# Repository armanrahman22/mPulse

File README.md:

M-PULSE-Server
==============

Code repository for the m-pulse code residing on the server

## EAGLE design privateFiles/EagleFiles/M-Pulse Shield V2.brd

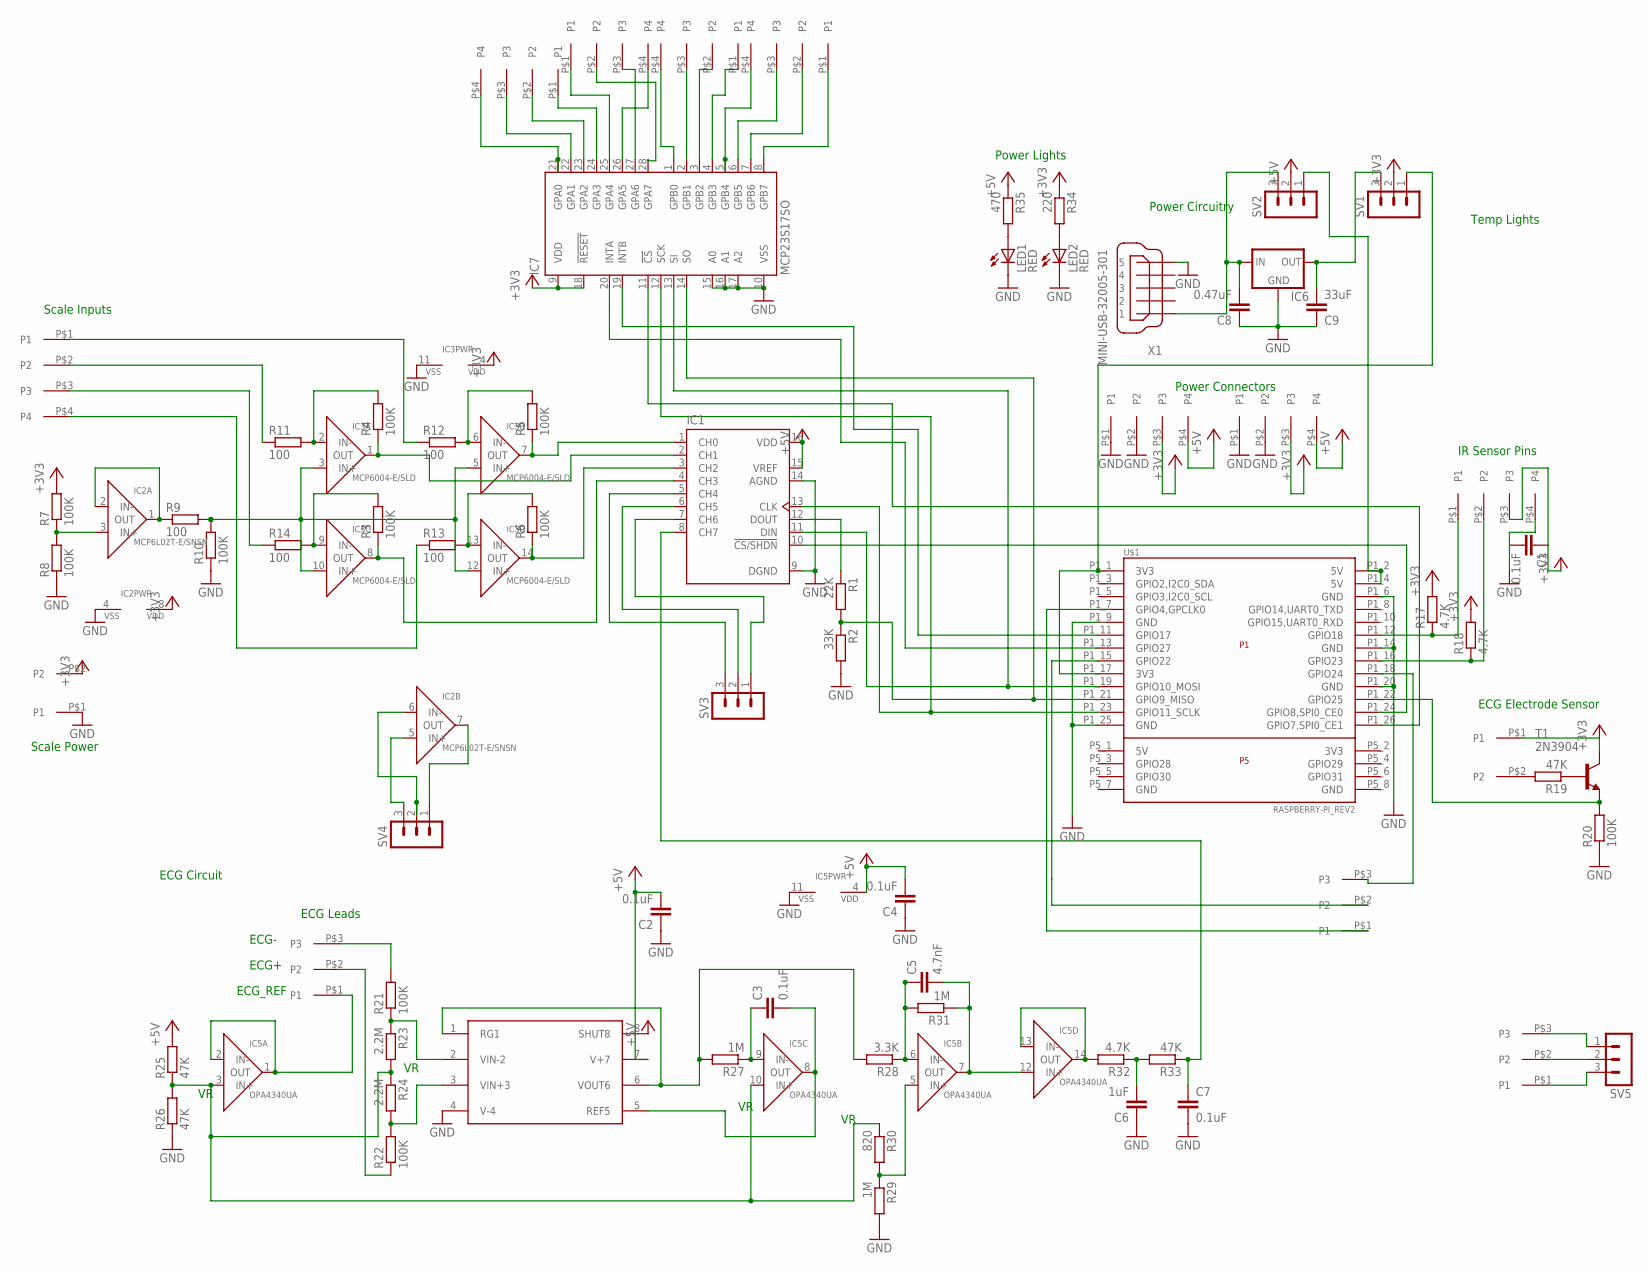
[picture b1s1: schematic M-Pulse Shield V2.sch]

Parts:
C1, C2, C3, C4, C7: 0.1uF; C0603
C5: 4.7nF; C0603
C6: 1uF; C0603
C8: 0.47uF; C0603
C9: 33uF; C0603
DIGITALPINS, DIGITALPINS1: 1776275-3
ECG_ES: 1776275-2
EKGLEADS: 1776275-3
I/O1, I/O2, I/O3, I/O4: 1776275-4
IC1: MCP3008; SOIC16N
IC2: MCP6L02T-E/SNSN; SO-08
IC3: MCP6004-E/SLD; SO14
IC4: INA321EAVSSOP-8; VSSOP-8
IC5: OPA4340UA; SO14
IC6: 78XXL
IC7: MCP23S17SO; SO28W
IR_I/O: 1776275-4
LED1, LED2: RED; LED_1206
POWEROUT, POWEROUT1: 1776275-4
R1: 22K; R0603
R2: 33K; R0603
R3, R4, R5, R6, R7, R8, R10, R20, R21, R22: 100K; R0603
R9, R11, R12, R13, R14: 100; R0603
R17, R18, R32: 4.7K; R0603
R19, R25, R26, R33: 47K; R0603
R23, R24: 2.2M; R0603
R27, R29, R31: 1M; R0603
R28: 3.3K; R0603
R30: 820; R0603
R34: 220; R0603
R35: 470; R0603
SV1, SV2, SV3, SV4, SV5: MA03-1
S_IN: 1776275-4
S_PWR: 1776275-2
T1: 2N3904; TO92
U$1: RASPBERRY-PI_REV2
X1: MINI-USB-32005-301; 32005-301

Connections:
+3V3: C1.1, ECG_ES.P$1 (P1), IC2.8 (VDD), IC3.4 (VDD), IC7.9 (VDD), IC7.18 (!RESET), IR_I/O.P$3 (P3), POWEROUT.P$3 (P3), POWEROUT1.P$3 (P3), R7.2, R17.2, R18.2, R34.1, SV1.2, S_PWR.P$2 (P2), T1.1 (C)
+5V: C2.2, C4.2, IC1.15 (VREF), IC1.16 (VDD), IC4.7 (V+7), IC4.8 (SHUT8), IC5.4 (VDD), POWEROUT.P$4 (P4), POWEROUT1.P$4 (P4), R25.2, R35.1, SV2.2
GND: C1.2, C2.1, C4.1, C6.1, C7.2, C8.1, C9.1, IC1.9 (DGND), IC1.14 (AGND), IC2.4 (VSS), IC3.11 (VSS), IC4.4 (V-4), IC5.11 (VSS), IC6.GND, IC7.10 (VSS), IC7.15 (A0), IC7.16 (A1), IC7.17 (A2), IR_I/O.P$4 (P4), LED1.C, LED2.C, POWEROUT.P$1 (P1), POWEROUT.P$2 (P2), POWEROUT1.P$1 (P1), POWEROUT1.P$2 (P2), R2.2, R8.1, R10.1, R20.1, R26.1, R29.2, S_PWR.P$1 (P1), U$1.P1_6 (GND), U$1.P1_9 (GND), U$1.P1_14 (GND), U$1.P1_20 (GND), U$1.P1_25 (GND), X1.5
unnamed: IC7.14 (SO), R1.2, R2.1, U$1.P1_21 (GPIO9_MISO)
unnamed: IC1.13 (CLK), IC7.12 (SCK), U$1.P1_23 (GPIO11_SCLK)
unnamed: IC1.12 (DOUT), R1.1
unnamed: IC1.11 (DIN), IC7.13 (SI), U$1.P1_19 (GPIO10_MOSI)
unnamed: IC1.10 (!CS/SHDN), U$1.P1_24 (GPIO8,SPI0_CE0)
unnamed: IC3.3 (IN+), IC3.5 (IN+), IC3.10 (IN+), IC3.12 (IN+), R9.2, R10.2
unnamed: R12.1, S_IN.P$1 (P1)
unnamed: R11.1, S_IN.P$2 (P2)
unnamed: IC1.4 (CH3), IC3.8 (OUT), R3.1
unnamed: IC1.3 (CH2), IC3.14 (OUT), R6.1
unnamed: IC1.2 (CH1), IC3.1 (OUT), R4.1
unnamed: I/O1.P$4 (P4), IC7.21 (GPA0)
unnamed: IC3.2 (IN-), R4.2, R11.2
unnamed: IC3.6 (IN-), R5.2, R12.2
unnamed: IC3.13 (IN-), R6.2, R13.2
unnamed: IC3.9 (IN-), R3.2, R14.2
unnamed: R13.1, S_IN.P$4 (P4)
unnamed: R14.1, S_IN.P$3 (P3)
unnamed: IC2.3 (IN+), R7.1, R8.2
unnamed: IC2.1 (OUT), IC2.2 (IN-), R9.1
unnamed: IC2.6 (IN-), SV4.2
unnamed: IC2.5 (IN+), SV4.3
unnamed: IR_I/O.P$1 (P1), R17.1, U$1.P1_12 (GPIO18)
unnamed: IR_I/O.P$2 (P2), R18.1, U$1.P1_16 (GPIO23)
unnamed: R19.1, T1.2 (B)
unnamed: ECG_ES.P$2 (P2), R19.2
unnamed: R20.2, T1.3 (E), U$1.P1_22 (GPIO25)
unnamed: IC4.2 (VIN-2), R21.1, R23.1
unnamed: IC5.13 (IN-), IC5.14 (OUT), R32.2
unnamed: IC4.3 (VIN+3), R22.2, R24.2
unnamed: EKGLEADS.P$3 (P3), R21.2
unnamed: EKGLEADS.P$2 (P2), R22.1
unnamed: EKGLEADS.P$1 (P1), IC5.1 (OUT), IC5.2 (IN-)
unnamed: C3.1, IC5.9 (IN-), R27.1
unnamed: I/O1.P$1 (P1), IC7.24 (GPA3)
unnamed: IC5.3 (IN+), IC5.10 (IN+), R23.2, R24.1, R25.1, R26.2, R30.1
unnamed: IC4.1 (RG1), IC4.6 (VOUT6), R27.2, R28.2
unnamed: IC5.5 (IN+), R29.1, R30.2
unnamed: C3.2, IC4.5 (REF5), IC5.8 (OUT)
unnamed: C5.1, IC5.6 (IN-), R28.1, R31.2
unnamed: C5.2, IC5.7 (OUT), IC5.12 (IN+), R31.1
unnamed: C6.2, R32.1, R33.2
unnamed: C7.1, IC1.8 (CH7), R33.1
unnamed: IC1.1 (CH0), IC3.7 (OUT), R5.1
unnamed: I/O1.P$2 (P2), IC7.23 (GPA2)
unnamed: I/O1.P$3 (P3), IC7.22 (GPA1)
unnamed: I/O2.P$4 (P4), IC7.26 (GPA5)
unnamed: I/O2.P$1 (P1), IC7.25 (GPA4)
unnamed: I/O2.P$2 (P2), IC7.28 (GPA7)
unnamed: I/O2.P$3 (P3), IC7.27 (GPA6)
unnamed: LED2.A, R34.2
unnamed: I/O3.P$4 (P4), IC7.1 (GPB0)
unnamed: I/O3.P$3 (P3), IC7.2 (GPB1)
unnamed: I/O3.P$2 (P2), IC7.3 (GPB2)
unnamed: I/O3.P$1 (P1), IC7.4 (GPB3)
unnamed: I/O4.P$4 (P4), IC7.5 (GPB4)
unnamed: I/O4.P$3 (P3), IC7.6 (GPB5)
unnamed: I/O4.P$2 (P2), IC7.7 (GPB6)
unnamed: IC7.19 (INTB), U$1.P1_11 (GPIO17)
unnamed: IC7.20 (INTA), U$1.P1_13 (GPIO27)
unnamed: IC7.11 (!CS), U$1.P1_26 (GPIO7,SPI0_CE1)
unnamed: IC1.5 (CH4), SV3.3
unnamed: IC1.6 (CH5), SV3.2
unnamed: IC1.7 (CH6), SV3.1
unnamed: IC2.7 (OUT), SV4.1
unnamed: DIGITALPINS.P$3 (P3), U$1.P1_18 (GPIO24)
unnamed: DIGITALPINS.P$2 (P2), U$1.P1_15 (GPIO22)
unnamed: DIGITALPINS.P$1 (P1), U$1.P1_7 (GPIO4,GPCLK0)
unnamed: C8.2, IC6.IN, SV2.3, X1.1
unnamed: SV2.1, U$1.P1_2 (5V), U$1.P1_4 (5V)
unnamed: C9.2, IC6.OUT, SV1.3
unnamed: SV1.1, U$1.P1_1 (3V3), U$1.P1_17 (3V3)
unnamed: I/O4.P$1 (P1), IC7.8 (GPB7)
unnamed: LED1.A, R35.2
unnamed: DIGITALPINS1.P$3 (P3), SV5.1
unnamed: DIGITALPINS1.P$1 (P1), SV5.3
unnamed: DIGITALPINS1.P$2 (P2), SV5.2

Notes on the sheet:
Scale Inputs
Scale Power
IR Sensor Pins
ECG Electrode Sensor
Power Lights
ECG Circuit
ECG Leads
ECG+
ECG-
ECG_REF
Power Circuitry
Power Connectors
Temp Lights

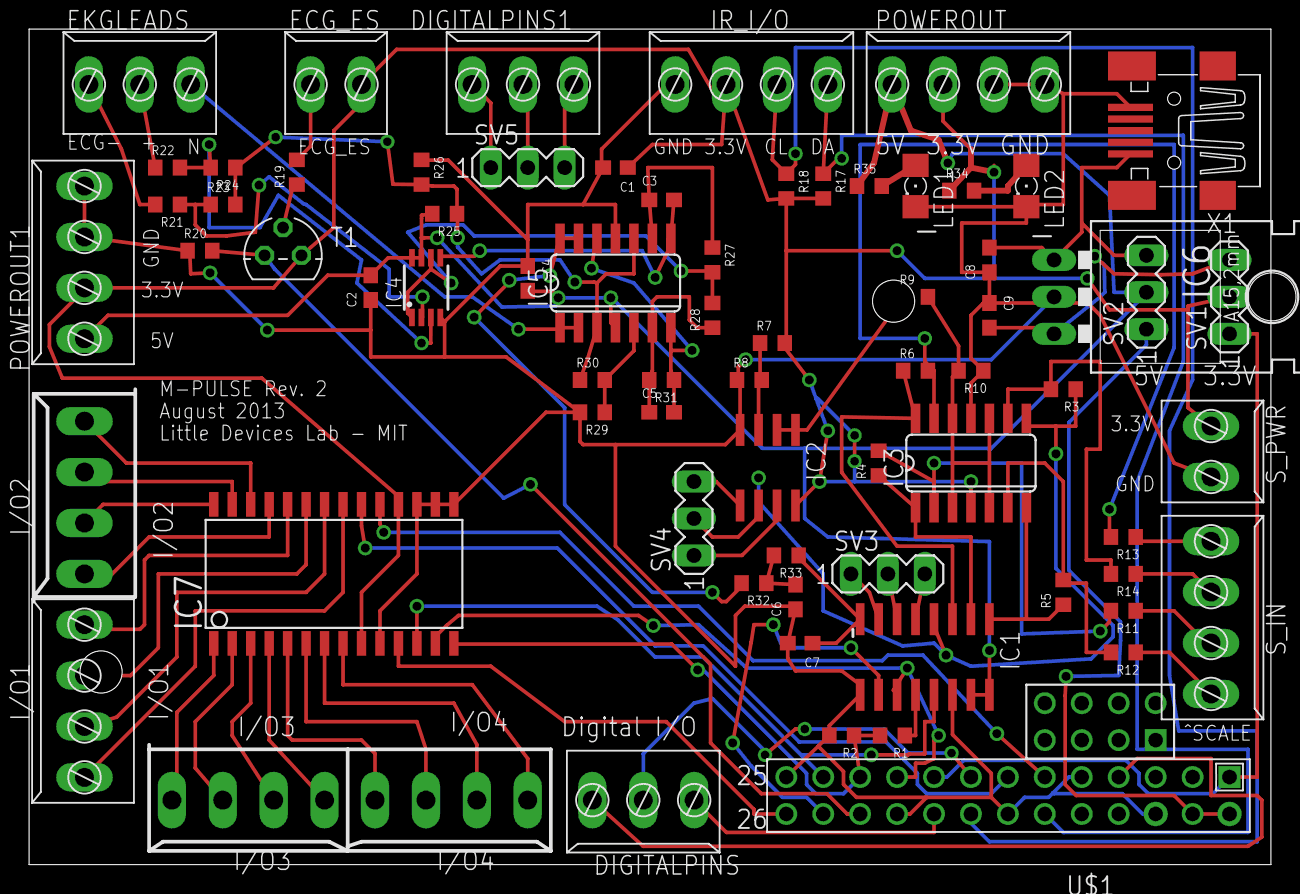
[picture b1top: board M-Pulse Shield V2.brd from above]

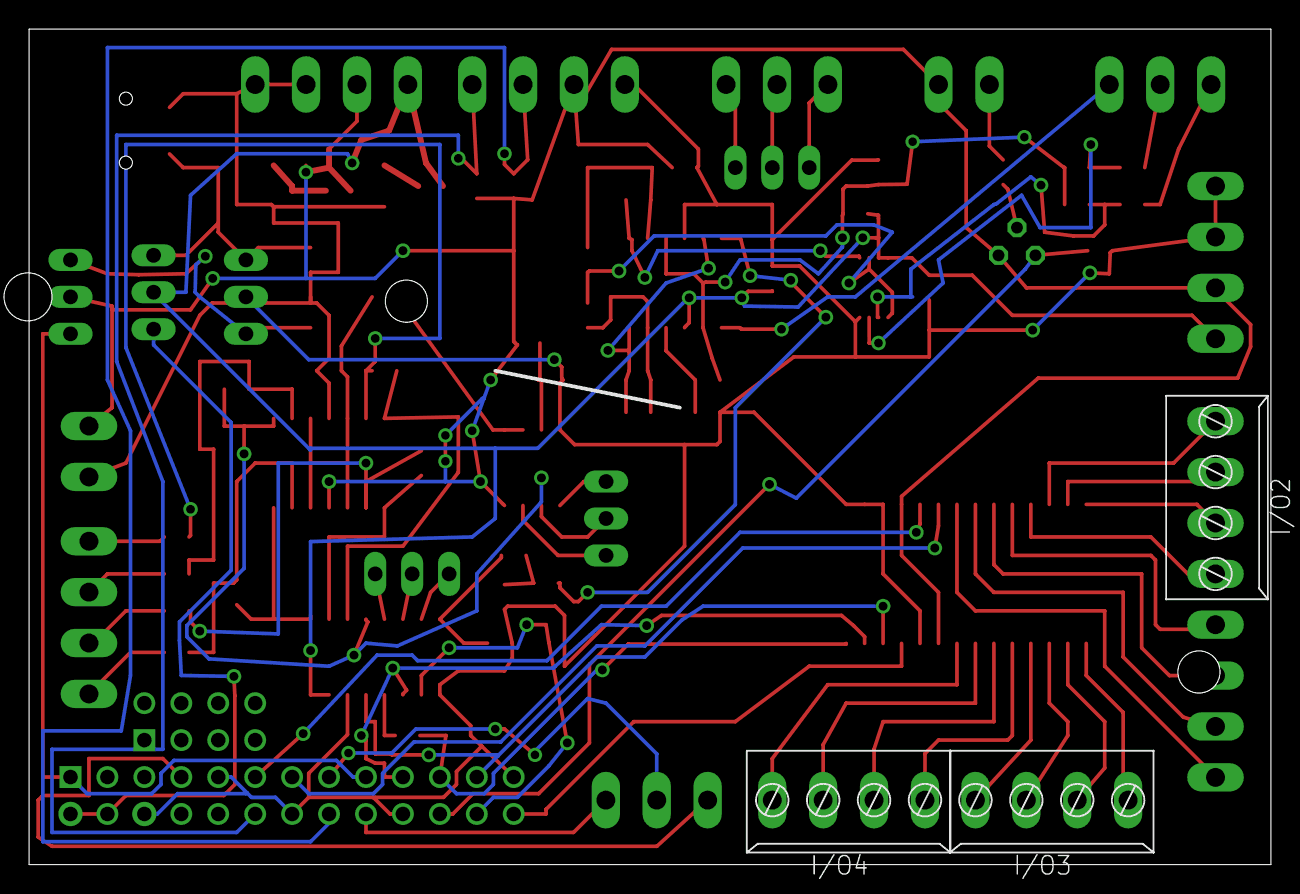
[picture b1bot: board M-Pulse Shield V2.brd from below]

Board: 2 copper layers, 85.4 x 57.5 mm, 72 parts (3 on the bottom side), 80 nets.

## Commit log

2015-02-15 added
2015-02-15 requirements added
2015-02-16 openshift revamp
